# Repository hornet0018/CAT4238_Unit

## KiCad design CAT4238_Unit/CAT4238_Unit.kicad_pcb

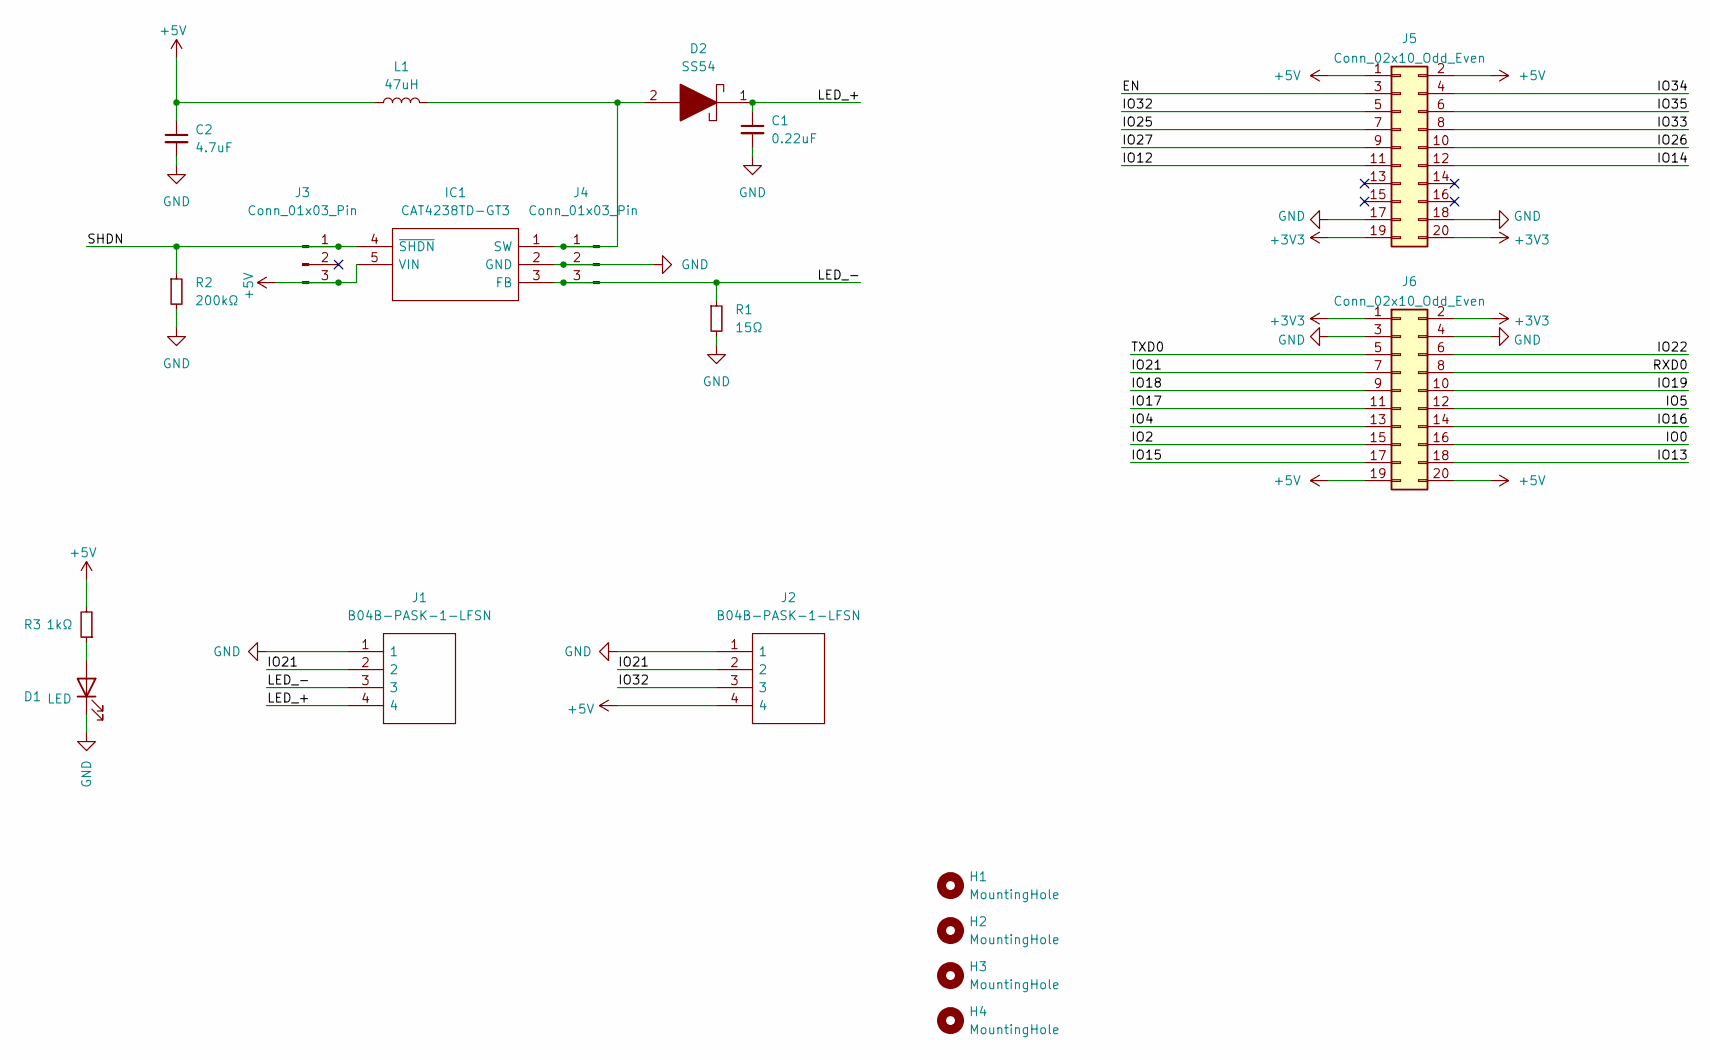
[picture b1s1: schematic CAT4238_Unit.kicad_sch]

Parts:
C1: 0.22uF; C_0603_1608Metric_Pad1.08x0.95mm_HandSolder
C2: 4.7uF; C_0603_1608Metric_Pad1.08x0.95mm_HandSolder
D1: LED; LED_0603_1608Metric_Pad1.05x0.95mm_HandSolder
D2: SS54; DIOM5026X262N; Manufacturer_Part_Number SS54
H1, H2, H3, H4: MountingHole; MountingHole_3.2mm_M3_Pad_Via
IC1: CAT4238TD-GT3; SOT95P280X100-5N; Manufacturer_Part_Number CAT4238TD-GT3; Mouser Part Number 698-CAT4238TDG
J1, J2: B04B-PASK-1-LFSN; B04BPASK1LFSN; Manufacturer_Part_Number B04B-PASK-1-LFSN; Mouser Part Number N/A
J3, J4: Conn_01x03_Pin; PinHeader_1x03_P2.54mm_Vertical
J5, J6: Conn_02x10_Odd_Even; PinHeader_2x10_P2.54mm_Vertical
L1: 47uH; L_Axial_L14.5mm_D5.8mm_P20.32mm_Horizontal_Fastron_HBCC
R1: 15Ω; R_0603_1608Metric_Pad0.98x0.95mm_HandSolder
R2: 200kΩ; R_0603_1608Metric_Pad0.98x0.95mm_HandSolder
R3: 1kΩ; R_0603_1608Metric_Pad0.98x0.95mm_HandSolder

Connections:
+3V3: J5.19, J5.20, J6.1, J6.2
+5V: C2.1, IC1.5 (VIN), J2.4, J3.3, J5.1, J5.2, J6.19, J6.20, L1.1, R3.2
/EN: J5.3
/IO0: J6.16
/IO2: J6.15
/IO4: J6.13
/IO5: J6.12
/IO12: J5.11
/IO13: J6.18
/IO14: J5.12
/IO15: J6.17
/IO16: J6.14
/IO17: J6.11
/IO18: J6.9
/IO19: J6.10
/IO21: J1.2, J2.2, J6.7
/IO22: J6.6
/IO25: J5.7
/IO26: J5.10
/IO27: J5.9
/IO32: J2.3, J5.5
/IO33: J5.8
/IO34: J5.4
/IO35: J5.6
/LED_+: C1.1, D2.1, J1.4
/LED_-: IC1.3 (FB), J1.3, J4.3, R1.1
/RXD0: J6.8
/SHDN: IC1.4 (~SHDN), J3.1, R2.1
/TXD0: J6.5
GND: C1.2, C2.2, D1.1 (K), IC1.2 (GND), J1.1, J2.1, J4.2, J5.17, J5.18, J6.3, J6.4, R1.2, R2.2
unnamed: D1.2 (A), R3.1
unnamed: D2.2, IC1.1 (SW), J4.1, L1.2

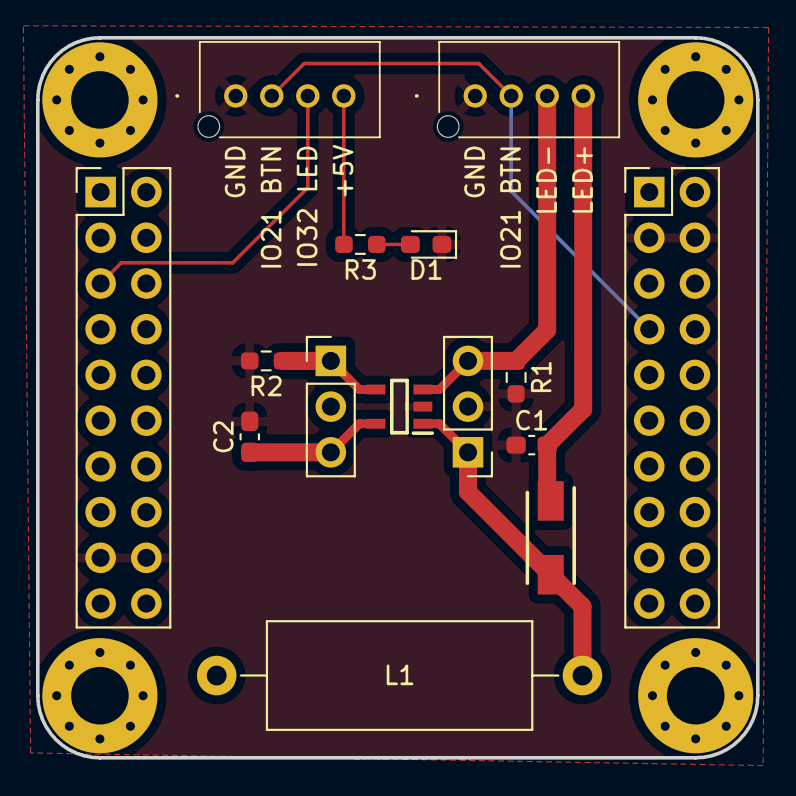
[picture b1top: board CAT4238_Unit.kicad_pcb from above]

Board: 6 copper layers, 40.0 x 40.0 mm, 19 parts (0 on the bottom side), 10 nets.

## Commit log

2023-12-29 Ordered from jlcpcb
